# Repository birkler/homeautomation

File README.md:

## Home Assistant (hassio) setup

### Philosophy
- All functions should work like "dumb" devices
- All home automation should work without internet connection
- Prefer hardwired; No WiFi dropouts/insecurity + POE can have central battery backup

### Router:
Port forward ext:443->int:8123
Static IPs for hardwired Raspberry ETH MAC

duckdns.org

17580montero.com -> birklerhome.duckdns.org

### Device Tree
```
- HomeAssistant (RaspberryPI)
    - USB
        - ZWave (Zoos USB)
            - Honeywell Thermostat
                - Inside Temperature
                - Inside Humidity
                - Inside Set Temp
            - Lights x10
            - Lights dimmable x25
            - Motion Sensor with Temp
                - Drive Way Motion
            - Lights with occupancy sensor
                - Motion Hallway
                - Motion Garage
                - Motion Bath
                - Motion Guest Bath
                - Motion Master Bath

        - Uninteruptible Power Supply
            - Line voltage
            - Run time
            - Load %

    - ETHERNET
        - Self - Raspbery Pi 4 (POE) [192.168.1.52]
        - Unifi Gateway+24Port POE switch
        - WIFI UniFi
            - Amazon ECHO
            - Amazon Ring Doorbell
            - ChromeCasts
            - Mobile Devices (HomeAssistant)
            - Roomba [192.168.1.61]
            - Wall Dashboard: FireTable 10HD + Kiosk Mode
                - Camera sensor
                - Motion Detector
                - Luminance Sensor
            - Jura Coffee Controller (does not work)

        - ESPHome Garage Doors  (POE)
            - Cover Twin
                - Sensor Closed Reed Switch 
                - Sensor Open  Reed Switch
                - Cover UP/STOP/DOWN
            - Cover Single
                - Sensor Closed Reed Switch 
                - Sensor Open  Reed Switch
                - Cover UP/STOP/DOWN
            - HC-SR04 UltraSonic Ranger
                - Car Occupancy 1
            - HC-SR04 UltraSonic Ranger
                - Car Occupancy 2

        - ESPHome Garage Monitor  (POE)
            - CT-clamp SCT-013-000
                - Dryer Current 
                    - Dryer On/Off
            - CT-clamp SCT-013-000
                - Washer Current 
                    - Washer On/Off
            - Doors Reed Switches (input):
                Door Outside,
                Door Interior
                Gate Exterior

            - Smoke Alarm Signal (input)
            - Smoke Alarm Siren Trigger (output)

        - ESPHome Irrigation Controller
            - 6x Zones 24VAC relay output
            - Week Schedule with customisible duration per zone

        - Pentair Pool Ethenet gateway  (POE) [192.168.1.22]
            - ZigBee
                - Pentair Pool controller
                    - Pool Water Temperature
                    - SPA  Water Temperature
                    - Outside Temperature
                    - Switch Filter Pump
                    - Switch Waterfall
                    - Switch Jets
                    - SPA Thermostat
                    - Pool Thermostat
                    - Pool Fill Valve

        - Rainforest Energy Gateway (POE)  [192.168.1.59]
            - Zigbee
                - SDG&E Electrical Meter
                    - kW grid demand
                    - kWh net total use
        - SolarEdge Gateway  (POE)
            - Zigbee
                - SolarEdge Inverter
        - SolarEdge Inverter Modbus [192.168.1.60]
            - kW,A,Vac,Vdc, ...
        - TV Sony OLED 65"
        - TV Sony OLED 77"

``` 

Planning Future
- Gas Ulitity Meter
- Range Current Sensor
- PIR sensor kitchen
- Outside Cameras

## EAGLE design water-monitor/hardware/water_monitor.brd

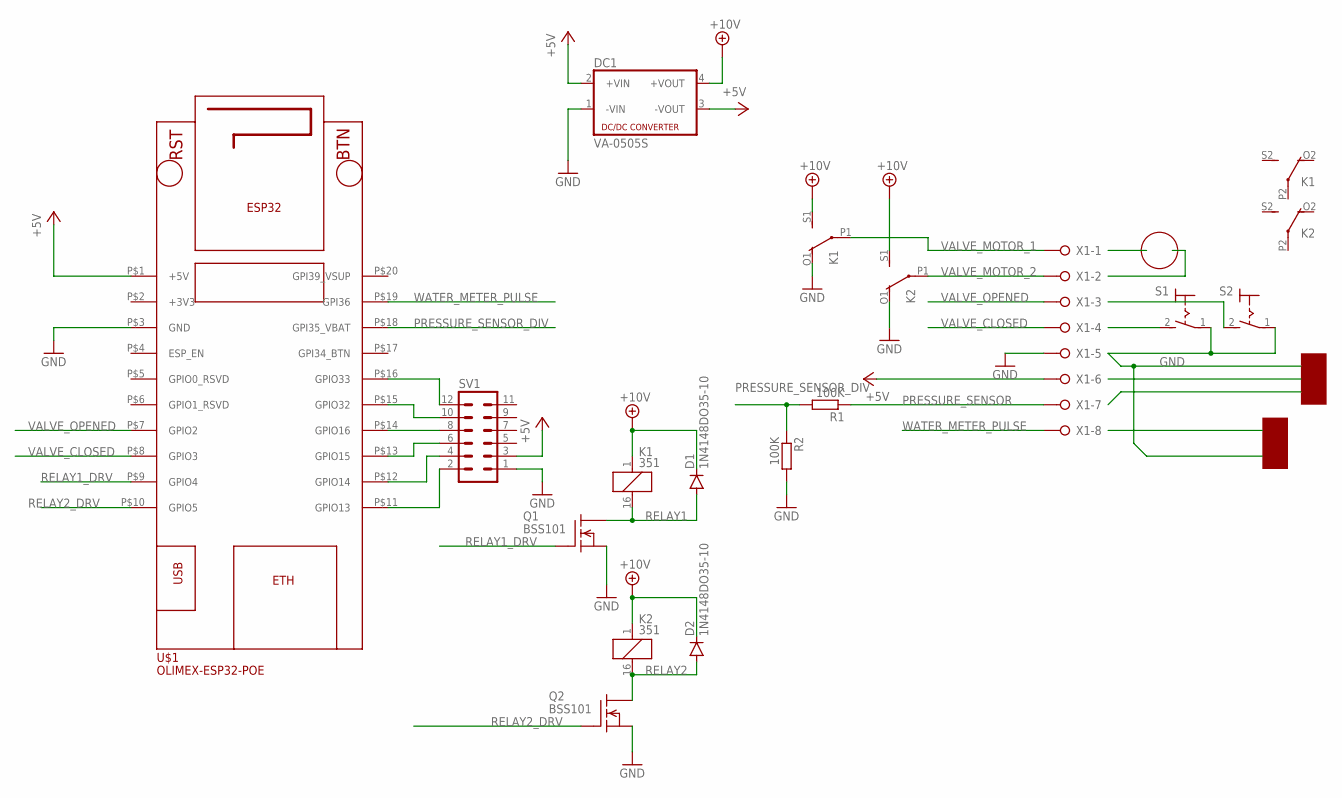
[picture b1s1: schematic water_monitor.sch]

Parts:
D1, D2: 1N4148DO35-10; DO35-10
DC1: VA-0505S; 4SIL
K1, K2: 351
Q1, Q2: BSS101; TO92
R1, R2: 100K; 0207/10
S1, S2: MS243
SV1: MA06-2
U$1: OLIMEX-ESP32-POE
X1: W237-08P; W237-8P

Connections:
+5V: DC1.2 (+VIN), DC1.3 (-VOUT), SV1.3, U$1.P$1 (+5V), X1.6
+10V: D1.C, D2.C, DC1.4 (+VOUT), K1.1, K1.S1 (S), K2.1, K2.S1 (S)
GND: DC1.1 (-VIN), K1.O1 (O), K2.O1 (O), Q1.1 (S), Q2.1 (S), R2.2, S1.1, S2.1, SV1.1, U$1.P$3 (GND), X1.5
unnamed: SV1.12, U$1.P$16 (GPIO33)
unnamed: SV1.2, U$1.P$11 (GPIO13)
unnamed: SV1.4, U$1.P$12 (GPIO14)
unnamed: SV1.6, U$1.P$13 (GPIO15)
unnamed: SV1.8, U$1.P$14 (GPIO16)
unnamed: SV1.10, U$1.P$15 (GPIO32)
PRESSURE_SENSOR: R1.1, X1.7
PRESSURE_SENSOR_DIV: R1.2, R2.1, U$1.P$18 (GPI35_VBAT)
RELAY1: D1.A, K1.16 (2), Q1.3 (D)
RELAY1_DRV: Q1.2 (G), U$1.P$9 (GPIO4)
RELAY2: D2.A, K2.16 (2), Q2.3 (D)
RELAY2_DRV: Q2.2 (G), U$1.P$10 (GPIO5)
VALVE_CLOSED: U$1.P$8 (GPIO3), X1.4
VALVE_MOTOR_1: K1.P1, X1.1
VALVE_MOTOR_2: K2.P1, X1.2
VALVE_OPENED: U$1.P$7 (GPIO2), X1.3
WATER_METER_PULSE: U$1.P$19 (GPI36), X1.8

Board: 2 copper layers, 14 parts (0 on the bottom side), 20 nets, no tracks yet.

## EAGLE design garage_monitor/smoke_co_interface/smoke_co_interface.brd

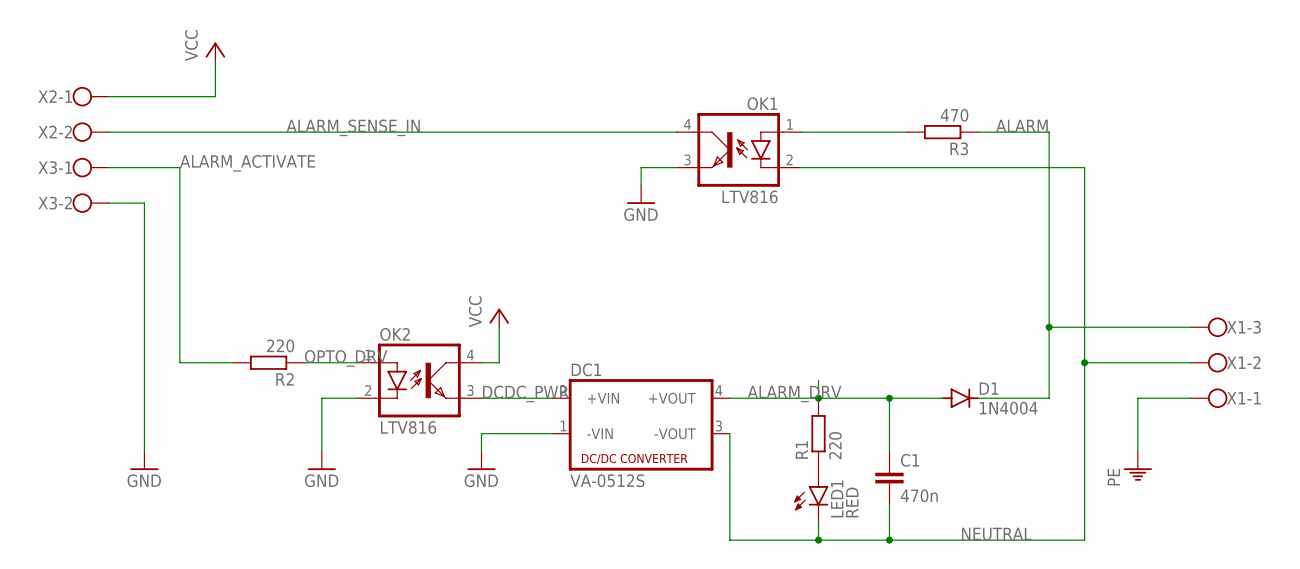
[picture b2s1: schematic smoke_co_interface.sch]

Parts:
C1: 470n; C050-035X075
D1: 1N4004; DO41-10
DC1: VA-0512S; 4SIL
LED1: RED; LED3MM
OK1, OK2: LTV816; DIL04
R1, R2: 220; 0207/10
R3: 470; 0207/10
X1: W237-103
X2, X3: W237-102

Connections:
ALARM: D1.C, R3.1, X1.3
ALARM_ACTIVATE: R2.2, X3.1
ALARM_DRV: C1.1, D1.A, DC1.4 (+VOUT), R1.2
ALARM_SENSE: OK1.1 (A), R3.2
ALARM_SENSE_IN: OK1.4 (COL), X2.2
DCDC_PWR: DC1.2 (+VIN), OK2.3 (EMIT)
GND: DC1.1 (-VIN), OK1.3 (EMIT), OK2.2 (C), X3.2
unnamed: LED1.A, R1.1
NEUTRAL: C1.2, DC1.3 (-VOUT), LED1.K (C), OK1.2 (C), X1.2
OPTO_DRV: OK2.1 (A), R2.1
PE: X1.1
VCC: OK2.4 (COL), X2.1

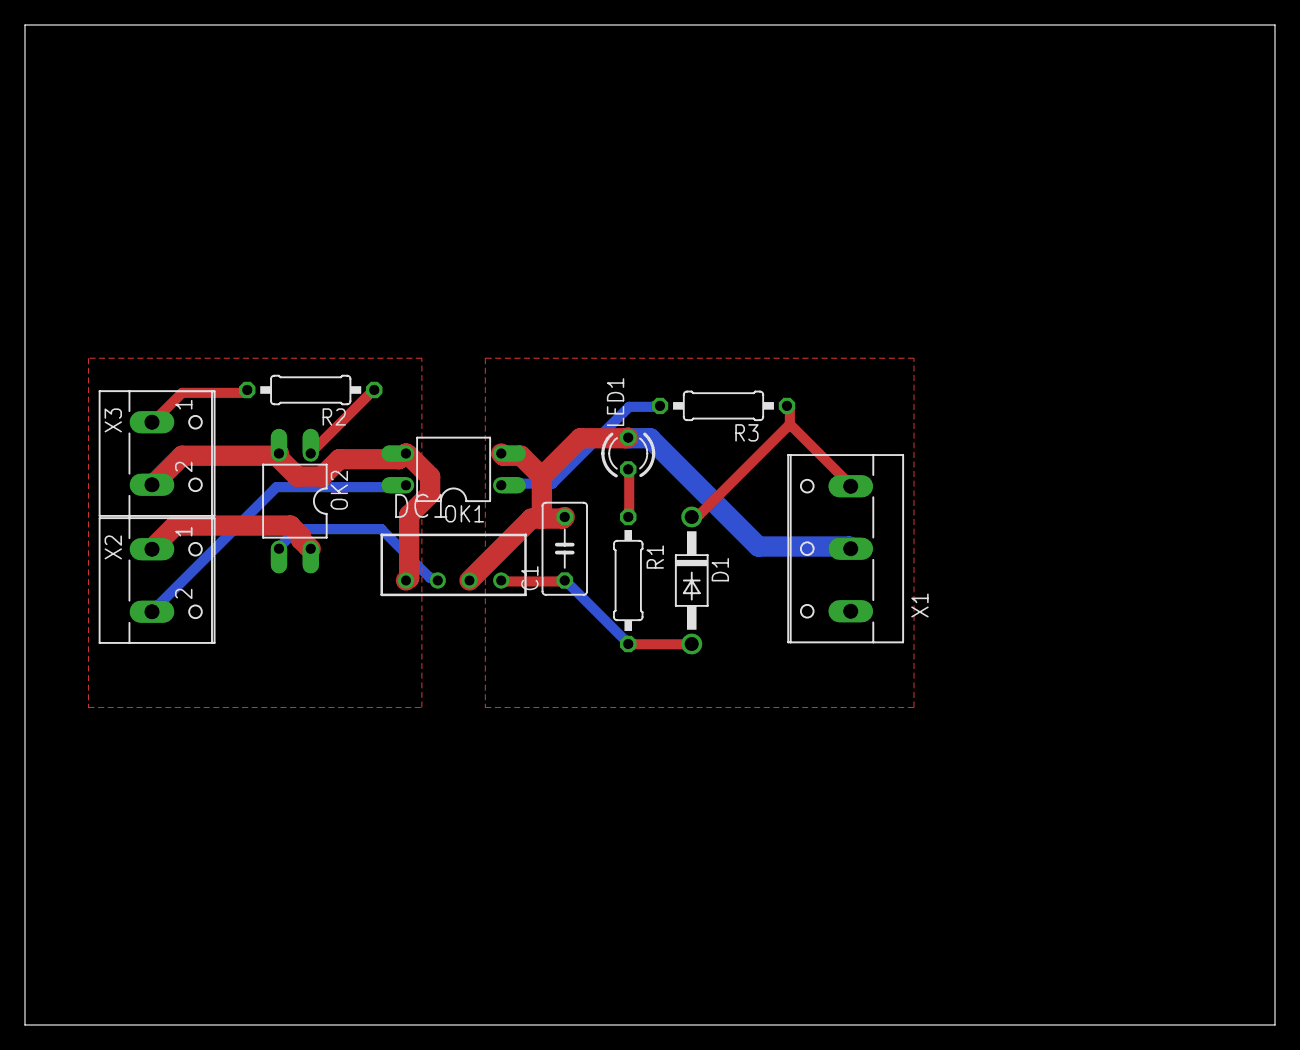
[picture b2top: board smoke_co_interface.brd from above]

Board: 2 copper layers, 100.0 x 80.0 mm, 12 parts (0 on the bottom side), 11 nets.

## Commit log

2020-08-25 First rev on github
2020-09-04 Latest changes
2021-01-15 add washer finished logic
2021-01-26 monitor:add timeout before sending dryer off.
2021-03-05 irrigation start
2021-03-09 updates to irrigation module
2021-03-11 update irrigation
2021-03-11 irrigation:check day of week and match to schedule. Update delay to minutes
2021-03-15 update some sensor values. fix garage safety beam. add status of connection.
2021-06-27 Add static IP addresses
2021-08-31 irrigation:use select components instead of +- switches.
2021-09-08 fresh_air:add electrical. update config.
2021-10-01 updates.
2022-03-06 update garage monitor to support smoke/co alarm.
2022-03-16 use analog_threshold for monitor and garage doors. update some pinout for fresh air controller.
2022-03-18 some updates.
2022-07-12 water monitor stuff.
2022-10-28 updates to device tree.
2022-11-30 update units and state_class.
